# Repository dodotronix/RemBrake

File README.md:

# RemBrake - remote brake system for handbikes 

## Introduction
- TODO explain what the RemBrake, why we decided to create this project

### Assembling RemBrake
- TODO explain how to use the kicad data (use html ibom in web browser)
- TODO how to solder the modules on the RemBrake PCB
- TODO how to connect the wires

## Notes
* Pay attention that all the connectors are well soldered to the board.

### Prepare the module 
1) load the circuitpython to the QT Py RP2040
2) press and hold BOOT button and then press RST button
3) you should see now RPI partition mounted to your PC 
4) download CircuitPython bootloader (.uf2 file) from [circuitpython.org](https://circuitpython.org/board/adafruit_qtpy_rp2040/) 
5) drag and drop the file onto the partition
6) it takes few moments and you should see your partition name turn to CIRCUITPYTHON

### Upload RemBrake files + necessary modules
1) go to the folder fw folder
2) run $ make prepare
3) move the folder target to your CIRCPITPYTHON partition

## Features
- TODO how the PCB behaves (charging, running, error)
- TODO what the different colors mean

## About the system
### System's Block Diagram (BD) 
### System's Finite State Machine (FSM)

## Possible further development
- Bidirectional remote contoller that the assistant can see the battery status
- Accelerometer feedback, to adjust braking power according to the situation
- Using hydraulic piston actuator to move with the brake directly, which could shrink significantly the size of the package
- designing custom usb-c charger to avoid the hustle with unprecise power management of the chinese module

## Development

# ISSUES 
## Hardware
* When the brake power is cut, the display turns off but the shift register
inside stays powered enough to retain its latched state; as a result, when the
LED bar is powered again it lights from the old data and continues glowing for
up to 8s.
* The transition from charging to running is too slow, so reverse current is
feeding the base of the state-switching transistor and back-driving it;
swapping in a Schottky diode (or regular diode) with a higher forward drop
would block that reverse current and fix the issue.

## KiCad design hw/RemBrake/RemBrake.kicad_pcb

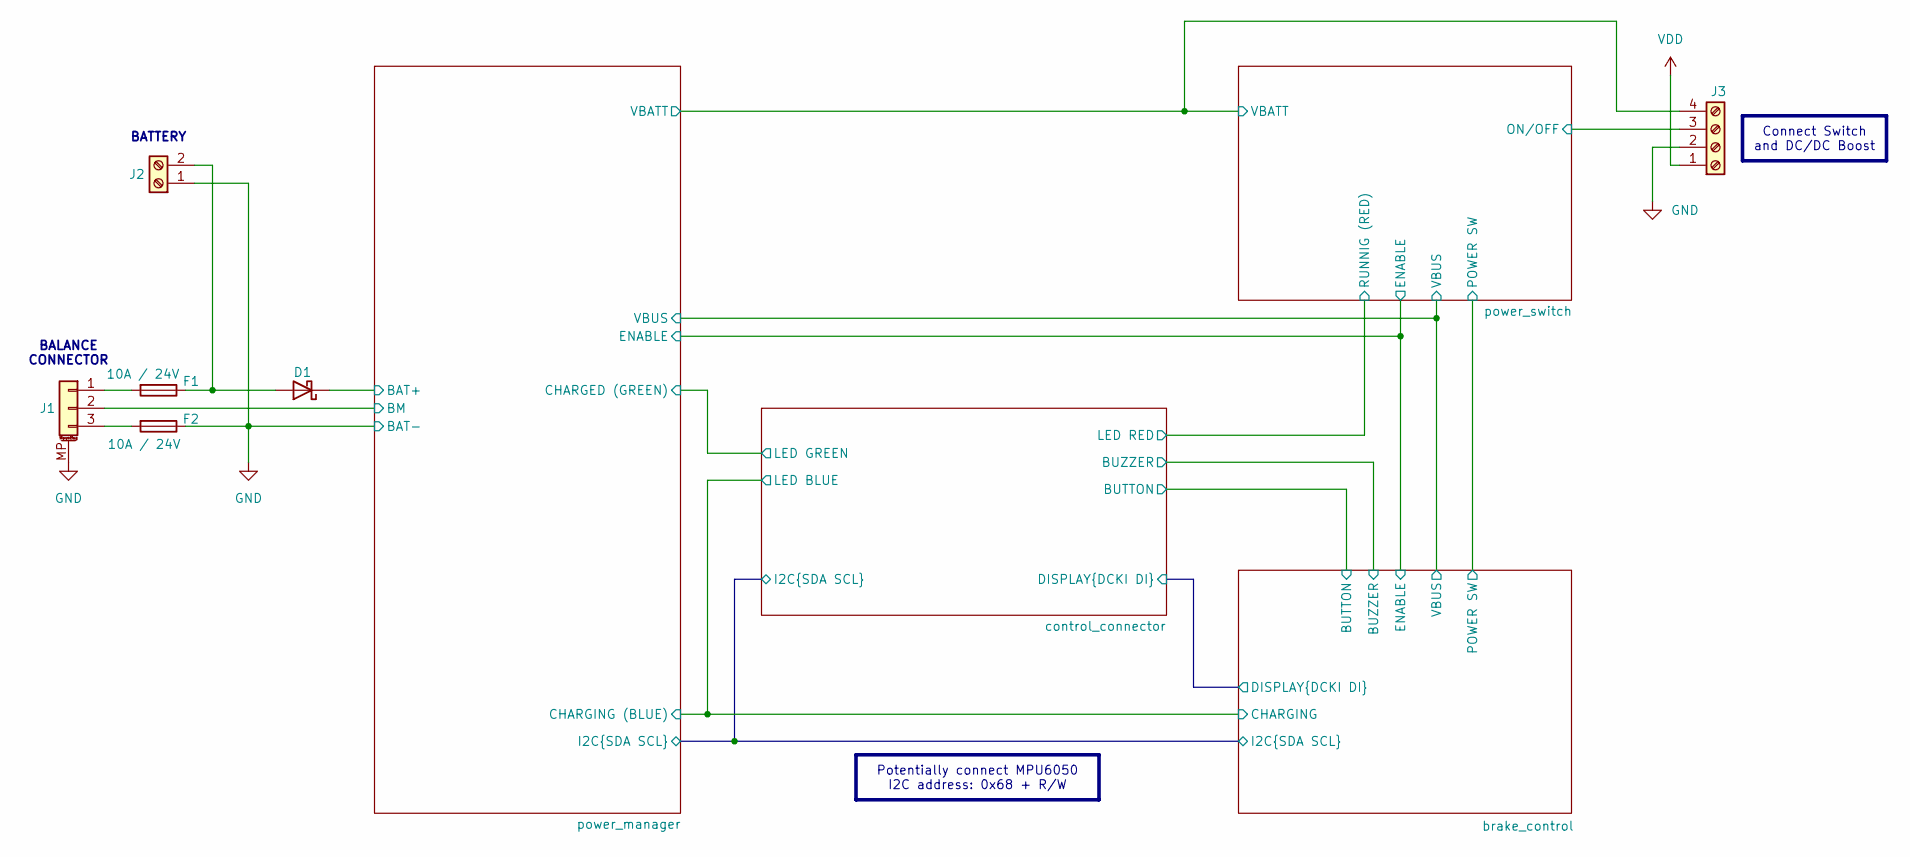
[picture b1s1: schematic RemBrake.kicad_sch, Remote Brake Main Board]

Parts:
D1: MBR0520; D_SMA
F1, F2: 10A / 24V; Fuse_1206_3216Metric_Pad1.42x1.75mm_HandSolder
J1: Conn_01x03_MountingPin; JST_XH_S3B-XH-SM4-TB_1x03-1MP_P2.50mm_Horizontal
J2: Screw_Terminal_01x02; TerminalBlock_Phoenix_MKDS-1,5-2_1x02_P5.00mm_Horizontal
J3: Screw_Terminal_01x04; TerminalBlock_Phoenix_MPT-0,5-4-2.54_1x04_P2.54mm_Horizontal

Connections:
/power_manager/BAT+: D1.1 (K); also elsewhere on the board
/power_manager/BM: J1.2; also elsewhere on the board
/power_manager/VBATT: J3.4; also elsewhere on the board
/power_switch/ON/OFF: J3.3; also elsewhere on the board
GND: F2.1, J1.MP (MountPin), J2.1, J3.2; also elsewhere on the board
unnamed: D1.2 (A), F1.1, J2.2
unnamed: F1.2, J1.1
unnamed: F2.2, J1.3
VDD: J3.1; also elsewhere on the board

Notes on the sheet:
BATTERY
BALANCE CONNECTOR
Potentially connect MPU6050 I2C address: 0x68 + R/W
Connect Switch and DC/DC Boost

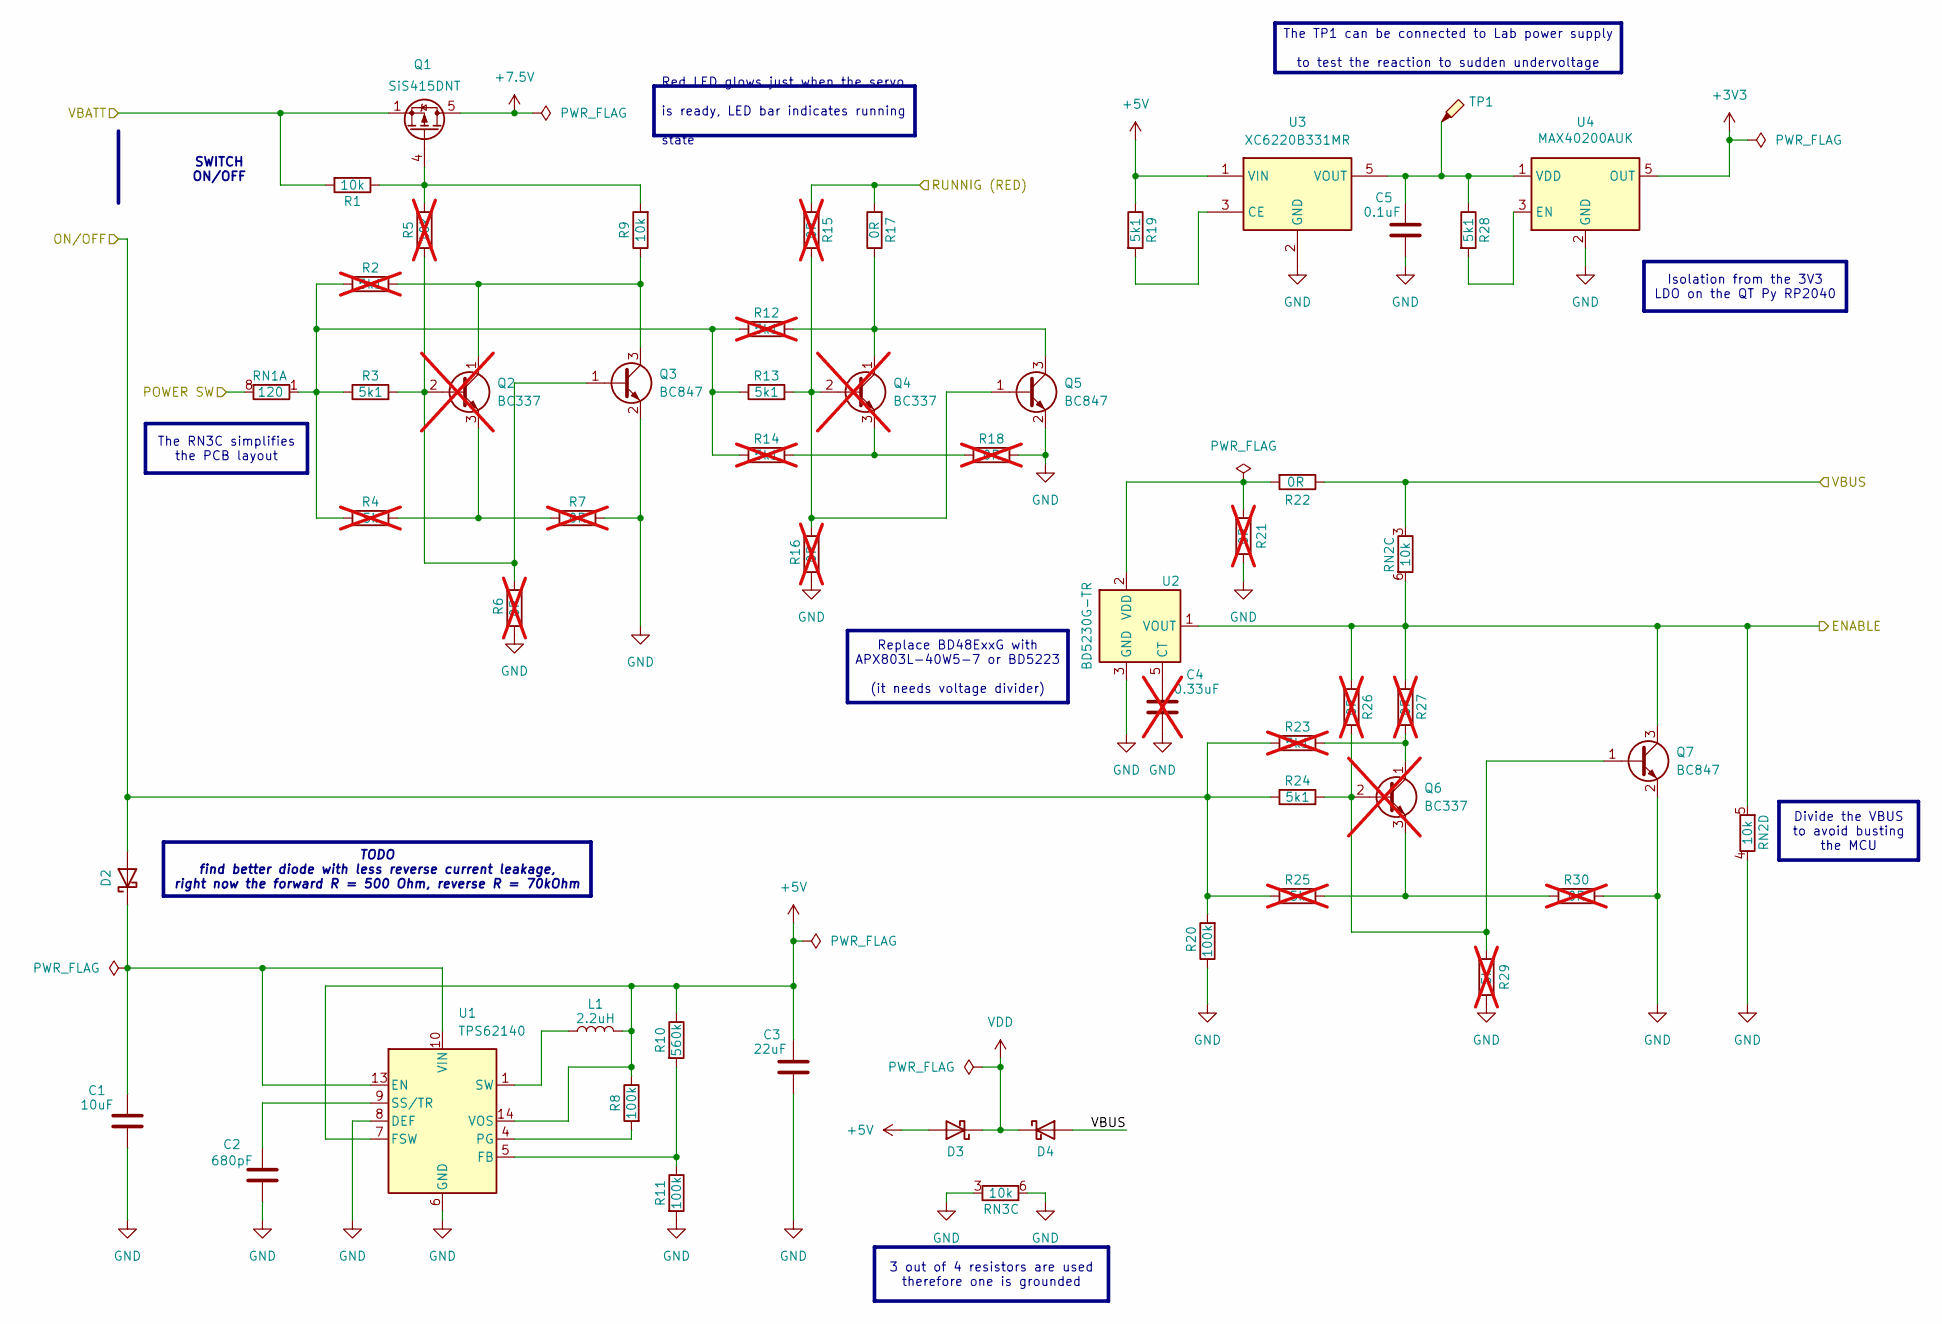
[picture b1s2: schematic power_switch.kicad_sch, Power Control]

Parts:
C1: 10uF; C_0805_2012Metric_Pad1.18x1.45mm_HandSolder
C2: 680pF; C_0805_2012Metric_Pad1.18x1.45mm_HandSolder
C3: 22uF; C_0805_2012Metric_Pad1.18x1.45mm_HandSolder
C4: 0.33uF; C_0805_2012Metric_Pad1.18x1.45mm_HandSolder; not fitted
C5: 0.1uF; C_0805_2012Metric_Pad1.18x1.45mm_HandSolder
D2: MBR0520; D_SMA
D3, D4: MBR0520; D_SOD-123
L1: 2.2uH; L_1008_2520Metric_Pad1.43x2.20mm_HandSolder
Q1: SiS415DNT; Vishay_PowerPAK_1212-8_Single
Q2, Q4, Q6: BC337; TO-92_Inline; not fitted
Q3, Q5, Q7: BC847; SOT-23
R1, R9: 10k; R_0805_2012Metric_Pad1.20x1.40mm_HandSolder
R2, R12, R14, R23: 5k1; R_0805_2012Metric_Pad1.20x1.40mm_HandSolder; not fitted
R3, R13, R19, R24, R28: 5k1; R_0805_2012Metric_Pad1.20x1.40mm_HandSolder
R4, R25, R29: 5k; R_0805_2012Metric_Pad1.20x1.40mm_HandSolder; not fitted
R5: 10k; R_0805_2012Metric_Pad1.20x1.40mm_HandSolder; not fitted
R6, R7, R15, R16, R18, R21, R26, R27, R30: 0R; R_0805_2012Metric_Pad1.20x1.40mm_HandSolder; not fitted
R8, R11, R20: 100k; R_0805_2012Metric_Pad1.20x1.40mm_HandSolder
R10: 560k; R_0805_2012Metric_Pad1.20x1.40mm_HandSolder
R17, R22: 0R; R_0805_2012Metric_Pad1.20x1.40mm_HandSolder
RN1: 120; R_Array_Concave_4x0603
RN2, RN3: 10k; R_Array_Convex_4x0603
TP1: TestPoint_Probe; TestPoint_Pad_1.5x1.5mm
U1: TPS62140; VQFN-16-1EP_3x3mm_P0.5mm_EP1.68x1.68mm_ThermalVias
U2: BD5230G-TR; SOT-23-5
U3: XC6220B331MR; SOT-23-5
U4: MAX40200AUK; SOT-23-5

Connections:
+3V3: U4.5 (OUT); also elsewhere on the board
+5V: C3.1, D3.2 (A), L1.2, R8.1, R10.1, R19.1, U1.7 (FSW), U1.14 (VOS), U3.1 (VIN); also elsewhere on the board
+7.5V: Q1.5 (D); also elsewhere on the board
/brake_control/ENABLE: Q7.3 (C), R26.2, R27.2, RN2.5 (R4.2), RN2.6 (R3.2), U2.1 (VOUT); also elsewhere on the board
/brake_control/POWER SW: RN1.8 (R1.2); also elsewhere on the board
/control_connector/LED RED: R15.2, R17.2; also elsewhere on the board
/power_manager/VBATT: Q1.1 (S), Q1.2 (S), Q1.3 (S), R1.2; also elsewhere on the board
/power_switch/ON/OFF: D2.2 (A), R20.2, R23.1, R24.1, R25.1; also elsewhere on the board
/power_switch/VBUS: D4.2 (A), R22.1, RN2.3 (R3.1); also elsewhere on the board
GND: C1.2, C2.2, C3.2, C4.2, C5.2, Q3.2 (E), Q5.2 (E), Q7.2 (E), R6.1, R7.1, R11.2, R16.1, R18.1, R20.1, R21.2, R29.1, R30.1, RN2.4 (R4.1), RN3.3 (R3.1), RN3.6 (R3.2), U1.6 (GND), U1.8 (DEF), U1.15 (GND), U1.16 (GND), U1.17 (GND), U2.3 (GND), U3.2 (GND), U4.2 (GND); also elsewhere on the board
unnamed: C1.1, D2.1 (K), U1.10 (VIN), U1.11 (VIN), U1.12 (VIN), U1.13 (EN)
unnamed: L1.1, U1.1 (SW), U1.2 (SW), U1.3 (SW)
unnamed: Q1.4 (G), R1.1, R5.2, R9.2
unnamed: Q2.2 (B), Q3.1 (B), R3.2, R5.1, R6.2
unnamed: Q2.1 (C), Q3.3 (C), R2.2, R9.1
unnamed: Q2.3 (E), R4.2, R7.2
unnamed: Q4.2 (B), Q5.1 (B), R13.2, R15.1, R16.2
unnamed: Q4.1 (C), Q5.3 (C), R12.2, R17.1
unnamed: Q4.3 (E), R14.2, R18.2
unnamed: Q6.2 (B), Q7.1 (B), R24.2, R26.1, R29.2
unnamed: Q6.1 (C), R23.2, R27.1
unnamed: Q6.3 (E), R25.2, R30.2
unnamed: R2.1, R3.1, R4.1, R12.1, R13.1, R14.1, RN1.1 (R1.1)
unnamed: R10.2, R11.1, U1.5 (FB)
unnamed: R8.2, U1.4 (PG)
unnamed: C2.1, U1.9 (SS/TR)
unnamed: C4.1, U2.5 (CT)
unnamed: R21.1, R22.2, U2.2 (VDD)
unnamed: R19.2, U3.3 (CE)
unnamed: C5.1, R28.1, TP1.1, U3.5 (VOUT), U4.1 (VDD)
unnamed: R28.2, U4.3 (EN)
VDD: D3.1 (K), D4.1 (K); also elsewhere on the board

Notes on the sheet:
SWITCH ON/OFF
Divide the VBUS to avoid busting the MCU
Red LED glows just when the servo is ready, LED bar indicates running state
Replace BD48ExxG with APX803L-40W5-7 or BD5223 (it needs voltage divider)
TODO find better diode with less reverse current leakage, right now the forward R = 500 Ohm, reverse R = 70kOhm
Isolation from the 3V3 LDO on the QT Py RP2040
The TP1 can be connected to Lab power supply to test the reaction to sudden undervoltage
The RN3C simplifies the PCB layout
3 out of 4 resistors are used therefore one is grounded

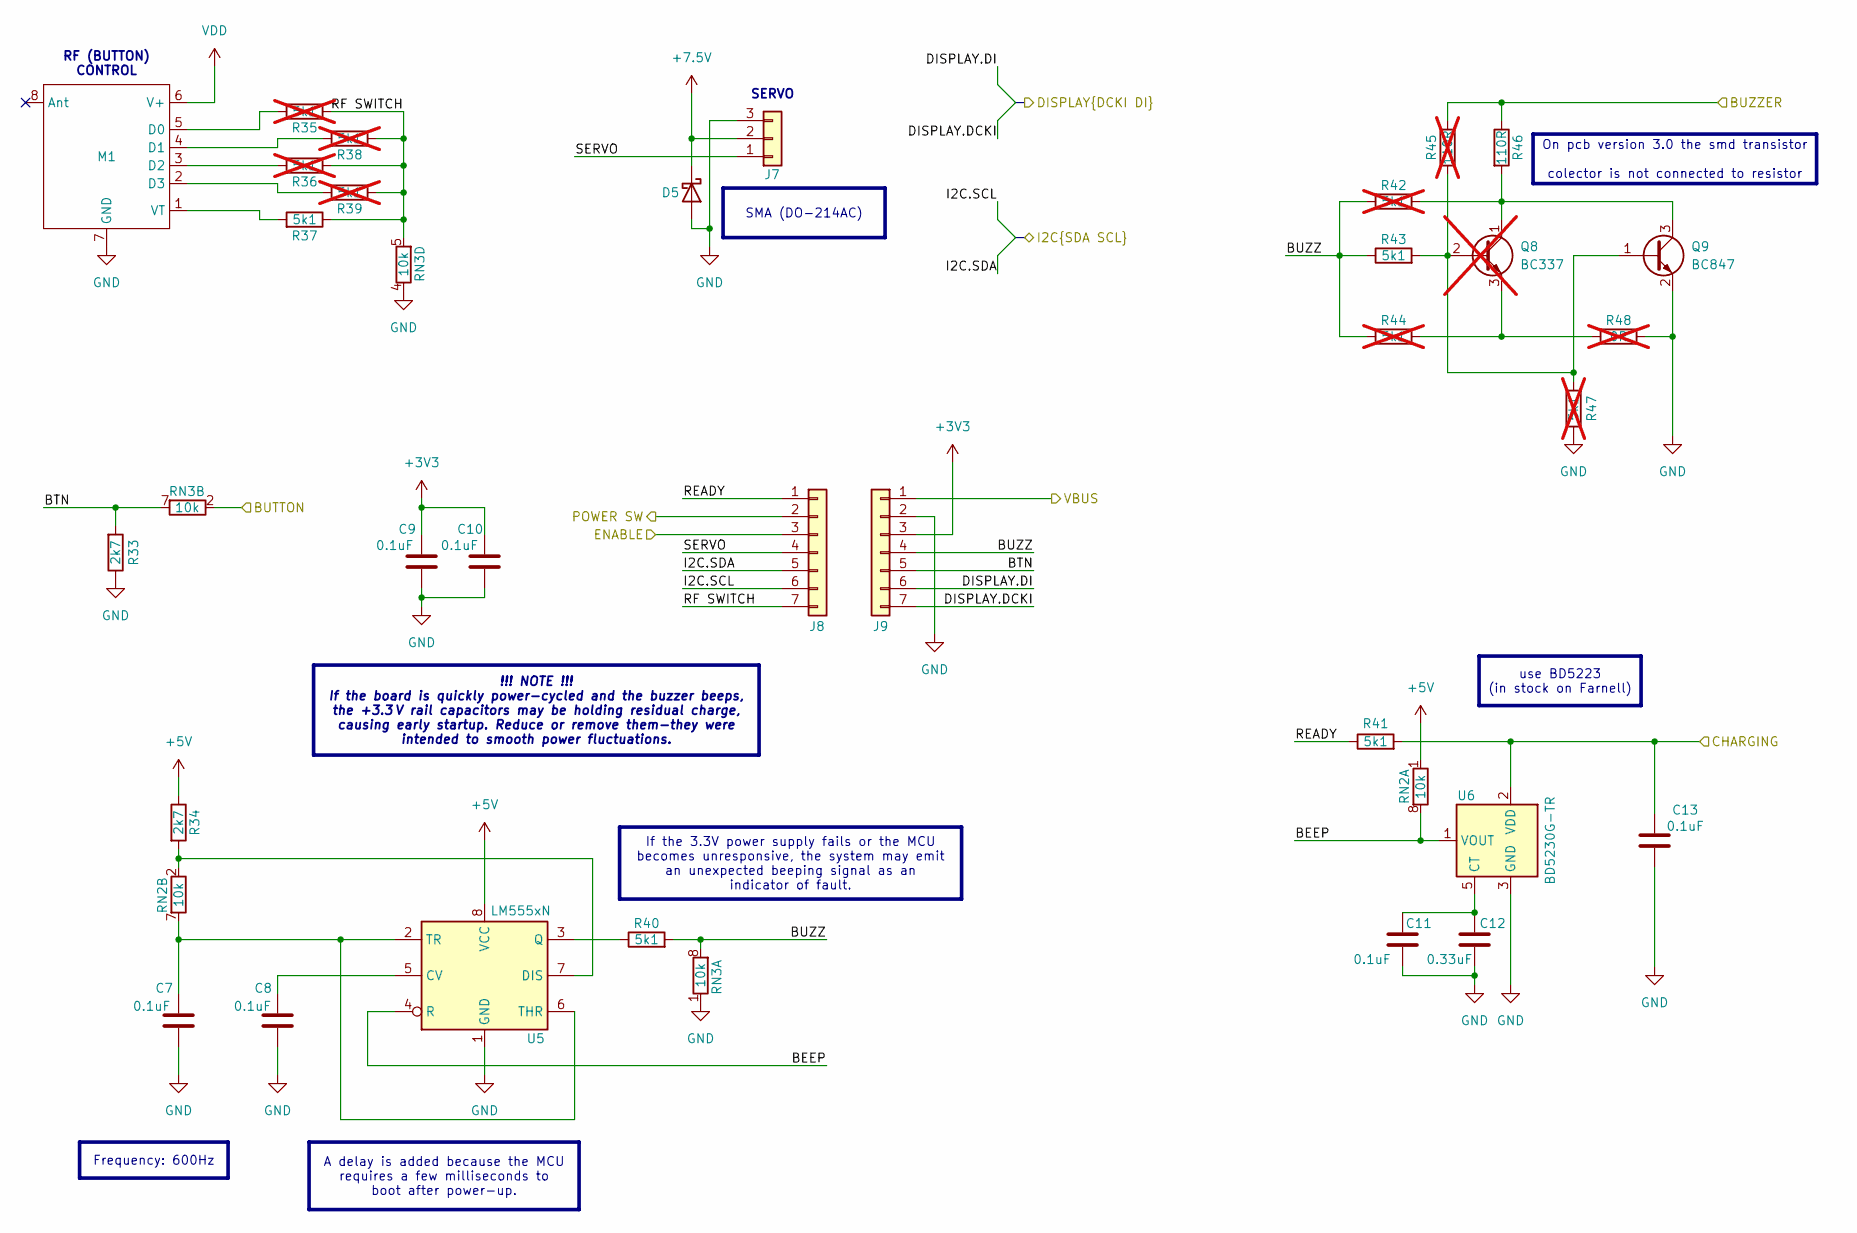
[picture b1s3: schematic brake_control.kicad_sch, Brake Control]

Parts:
C7, C8, C9, C10, C11, C13: 0.1uF; C_0805_2012Metric_Pad1.18x1.45mm_HandSolder
C12: 0.33uF; C_0805_2012Metric_Pad1.18x1.45mm_HandSolder
D5: SS1200; D_SMA
J7: Conn_01x03; PinHeader_1x03_P2.54mm_Vertical_SMD_Pin1Left
J8, J9: Conn_01x07; PinSocket_1x07_P2.54mm_Vertical_SMD_Pin1Left
M1: RF_controller
Q8: BC337; TO-92_Inline; not fitted
Q9: BC847; SOT-23
R33, R34: 2k7; R_0805_2012Metric_Pad1.20x1.40mm_HandSolder
R35, R36, R38, R39, R42, R44, R47: 5k1; R_0805_2012Metric_Pad1.20x1.40mm_HandSolder; not fitted
R37, R40, R41, R43: 5k1; R_0805_2012Metric_Pad1.20x1.40mm_HandSolder
R45: 110R; R_0805_2012Metric_Pad1.20x1.40mm_HandSolder; not fitted
R46: 110R; R_0805_2012Metric_Pad1.20x1.40mm_HandSolder
R48: 0R; R_0805_2012Metric_Pad1.20x1.40mm_HandSolder; not fitted
RN2, RN3: 10k; R_Array_Convex_4x0603
U5: LM555xN; DIP-8_W7.62mm
U6: BD5230G-TR; SOT-23-5

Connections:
+3V3: C9.1, C10.1, J9.3; also elsewhere on the board
+5V: R34.1, RN2.1 (R1.1), U5.8 (VCC); also elsewhere on the board
+7.5V: D5.1 (K), J7.2; also elsewhere on the board
/brake_control/BEEP: RN2.8 (R1.2), U5.4 (R), U6.1 (VOUT)
/brake_control/BTN: J9.5, R33.2, RN3.7 (R2.2)
/brake_control/BUZZ: J9.4, R40.2, R42.2, R43.1, R44.1, RN3.8 (R1.2)
/brake_control/CHARGING: C13.1, R41.2, U6.2 (VDD); also elsewhere on the board
/brake_control/DISPLAY.DCKI: J9.7; also elsewhere on the board
/brake_control/DISPLAY.DI: J9.6; also elsewhere on the board
/brake_control/ENABLE: J8.3; also elsewhere on the board
/brake_control/I2C.SCL: J8.6; also elsewhere on the board
/brake_control/I2C.SDA: J8.5; also elsewhere on the board
/brake_control/POWER SW: J8.2; also elsewhere on the board
/brake_control/READY: J8.1, R41.1
/brake_control/RF SWITCH: J8.7, R35.1, R36.1, R37.1, R38.1, R39.1, RN3.5 (R4.2)
/brake_control/SERVO: J7.1, J8.4
/control_connector/BUTTON: RN3.2 (R2.1); also elsewhere on the board
/control_connector/BUZZER: R45.1, R46.1; also elsewhere on the board
/power_switch/VBUS: J9.1; also elsewhere on the board
GND: C7.2, C8.2, C9.2, C10.2, C11.2, C12.2, C13.2, D5.2 (A), J7.3, J9.2, M1.7 (GND), Q9.2 (E), R33.1, R47.1, R48.1, RN3.1 (R1.1), RN3.4 (R4.1), U5.1 (GND), U6.3 (GND); also elsewhere on the board
unnamed: M1.5 (D0), R35.2
unnamed: M1.4 (D1), R38.2
unnamed: M1.3 (D2), R36.2
unnamed: M1.2 (D3), R39.2
unnamed: M1.1 (VT), R37.2
unnamed: Q8.2 (B), Q9.1 (B), R43.2, R45.2, R47.2
unnamed: Q8.1 (C), Q9.3 (C), R42.1, R46.2
unnamed: Q8.3 (E), R44.2, R48.2
unnamed: R34.2, RN2.2 (R2.1), U5.7 (DIS)
unnamed: C7.1, RN2.7 (R2.2), U5.2 (TR), U5.6 (THR)
unnamed: C8.1, U5.5 (CV)
unnamed: R40.1, U5.3 (Q)
unnamed: C11.1, C12.1, U6.5 (CT)
VDD: M1.6 (V+); also elsewhere on the board

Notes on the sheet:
SERVO
RF (BUTTON) CONTROL
SMA (DO-214AC)
!!! NOTE !!! If the board is quickly power-cycled and the buzzer beeps, the +3.3 V rail capacitors may be holding residual charge, causing early startup. Reduce or remove them-they were intended to smooth power fluctuations.
A delay is added because the MCU requires a few milliseconds to boot after power-up.
use BD5223 (in stock on Farnell)
Frequency: 600Hz
On pcb version 3.0 the smd transistor colector is not connected to resistor
If the 3.3V power supply fails or the MCU becomes unresponsive, the system may emit an unexpected beeping signal as an indicator of fault.

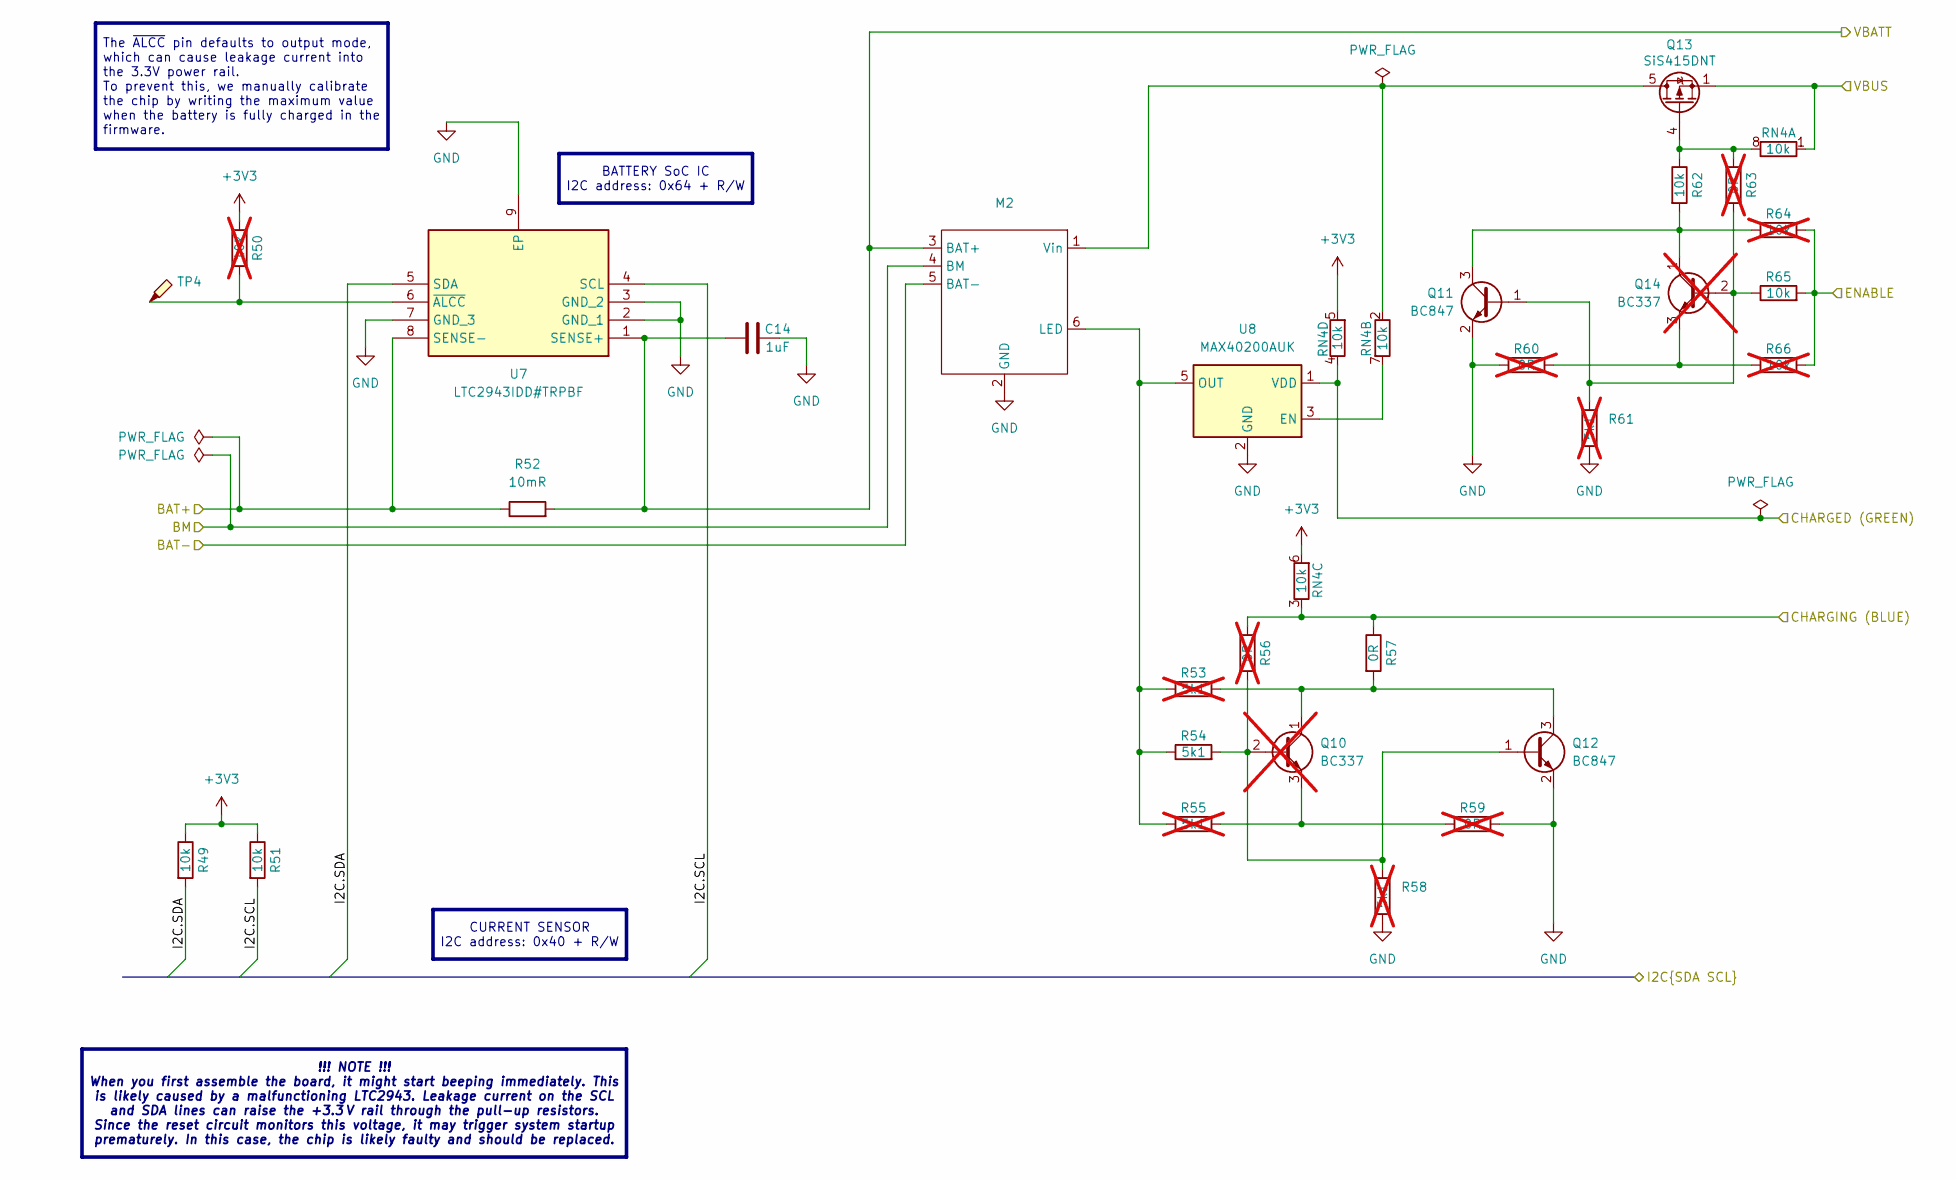
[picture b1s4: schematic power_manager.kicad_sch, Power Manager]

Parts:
C14: 1uF; C_0805_2012Metric_Pad1.18x1.45mm_HandSolder
M2: USBC_charger
Q10, Q14: BC337; TO-92_Inline; not fitted
Q11, Q12: BC847; SOT-23
Q13: SiS415DNT; Vishay_PowerPAK_1212-8_Single
R49, R51, R62, R65: 10k; R_0805_2012Metric_Pad1.20x1.40mm_HandSolder
R50, R64, R66: 10k; R_0805_2012Metric_Pad1.20x1.40mm_HandSolder; not fitted
R52: 10mR; R_2512_6332Metric_Pad1.40x3.35mm_HandSolder
R53, R55, R58, R61: 5k1; R_0805_2012Metric_Pad1.20x1.40mm_HandSolder; not fitted
R54: 5k1; R_0805_2012Metric_Pad1.20x1.40mm_HandSolder
R56, R59, R60, R63: 0R; R_0805_2012Metric_Pad1.20x1.40mm_HandSolder; not fitted
R57: 0R; R_0805_2012Metric_Pad1.20x1.40mm_HandSolder
RN4: 10k; R_Array_Convex_4x0603
TP4: TestPoint_Probe; TestPoint_Pad_1.5x1.5mm
U7: LTC2943IDD#TRPBF; DFN-8-1EP_3x3mm_P0.5mm_EP1.66x2.38mm; Mouser Part Number 584-LTC2943IDD#TRPBF
U8: MAX40200AUK; SOT-23-5

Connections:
+3V3: R49.1, R50.1, R51.1, RN4.5 (R4.2), RN4.6 (R3.2); also elsewhere on the board
/brake_control/CHARGING: R56.1, R57.1, RN4.3 (R3.1); also elsewhere on the board
/brake_control/ENABLE: R64.2, R65.2, R66.2; also elsewhere on the board
/brake_control/I2C.SCL: R51.2, U7.4 (SCL); also elsewhere on the board
/brake_control/I2C.SDA: R49.2, U7.5 (SDA); also elsewhere on the board
/control_connector/LED GREEN: RN4.4 (R4.1), U8.1 (VDD); also elsewhere on the board
/power_manager/BAT+: R52.1, U7.8 (SENSE-); also elsewhere on the board
/power_manager/BM: M2.4 (BM); also elsewhere on the board
/power_manager/VBATT: C14.2, M2.3 (BAT+), R52.2, U7.1 (SENSE+); also elsewhere on the board
/power_switch/VBUS: Q13.1 (S), Q13.2 (S), Q13.3 (S), RN4.1 (R1.1); also elsewhere on the board
GND: C14.1, M2.2 (GND), M2.5 (BAT-), Q11.2 (E), Q12.2 (E), R58.1, R59.1, R60.2, R61.1, U7.2 (GND_1), U7.3 (GND_2), U7.7 (GND_3), U7.9 (EP), U8.2 (GND); also elsewhere on the board
unnamed: M2.6 (LED), R53.1, R54.1, R55.1, U8.5 (OUT)
unnamed: M2.1 (Vin), Q13.5 (D), RN4.2 (R2.1)
unnamed: Q10.2 (B), Q12.1 (B), R54.2, R56.2, R58.2
unnamed: Q10.1 (C), Q12.3 (C), R53.2, R57.2
unnamed: Q10.3 (E), R55.2, R59.2
unnamed: Q11.1 (B), Q14.2 (B), R61.2, R63.2, R65.1
unnamed: Q11.3 (C), Q14.1 (C), R62.2, R64.1
unnamed: Q13.4 (G), R62.1, R63.1, RN4.8 (R1.2)
unnamed: Q14.3 (E), R60.1, R66.1
unnamed: RN4.7 (R2.2), U8.3 (EN)
unnamed: R50.2, TP4.1, U7.6 (~ALCC)

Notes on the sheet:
!!! NOTE !!! When you first assemble the board, it might start beeping immediately. This is likely caused by a malfunctioning LTC2943. Leakage current on the SCL and SDA lines can raise the +3.3 V rail through the pull-up resistors. Since the reset circuit monitors this voltage, it may trigger syst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
BATTERY SoC IC I2C address: 0x64 + R/W
The ~{ALCC} pin defaults to output mode, which can cause leakage current into the 3.3V power rail. To prevent this, we manually calibrate the chip by writing the maximum value when the battery is fully charged in the firmware.
CURRENT SENSOR I2C address: 0x40 + R/W

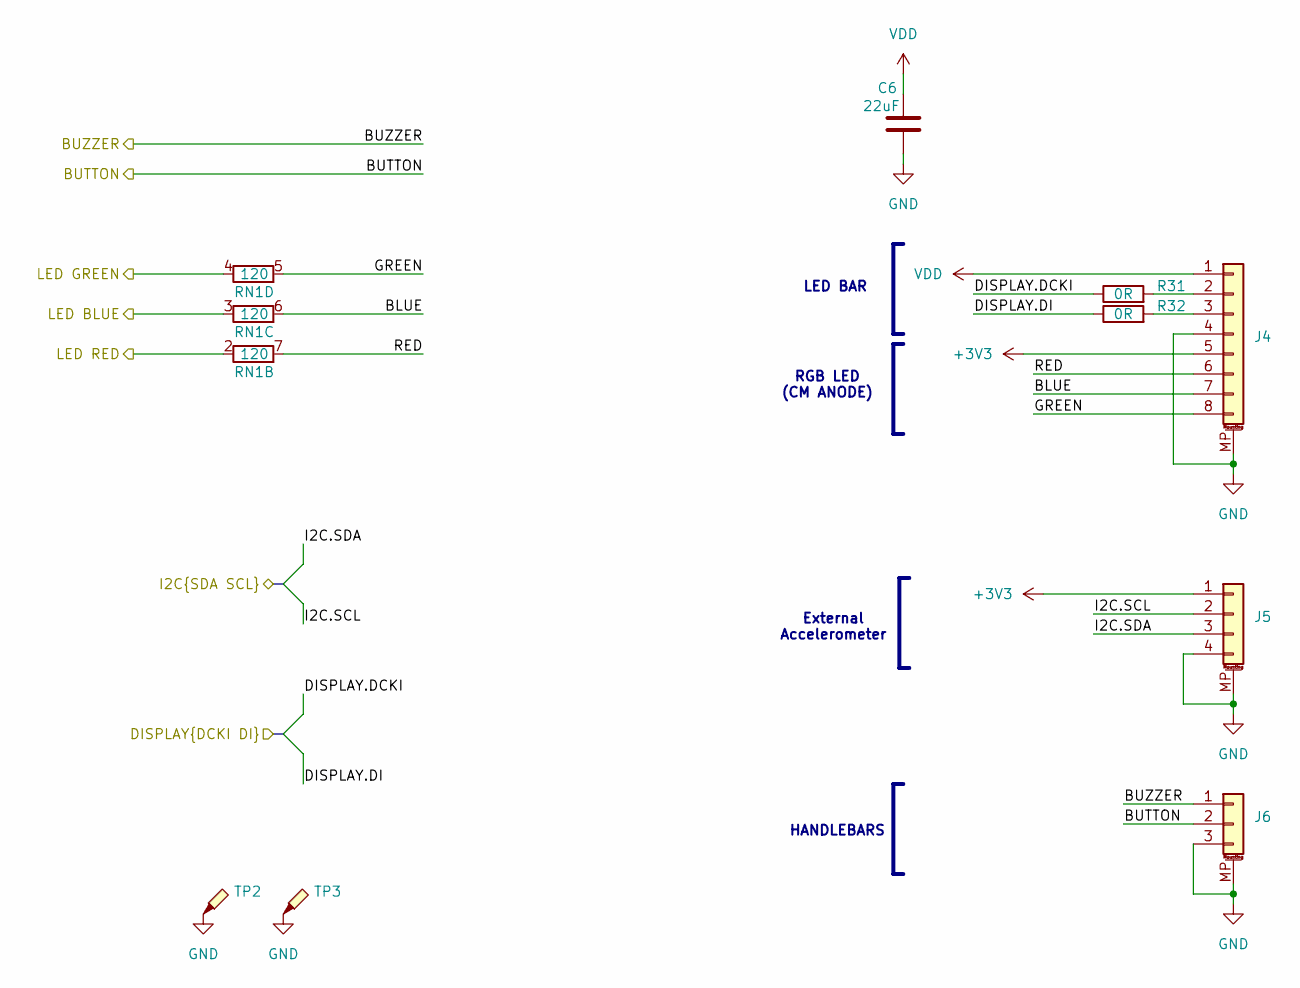
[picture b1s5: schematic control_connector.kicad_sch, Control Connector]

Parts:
C6: 22uF; C_0805_2012Metric_Pad1.18x1.45mm_HandSolder
J4: Conn_01x08_MountingPin; Molex_CLIK-Mate_502494-0870_1x08-1MP_P2.00mm_Horizontal
J5: Conn_01x04_MountingPin; Molex_CLIK-Mate_502494-0470_1x04-1MP_P2.00mm_Horizontal
J6: Conn_01x03_MountingPin; Molex_CLIK-Mate_502494-0370_1x03-1MP_P2.00mm_Horizontal
R31, R32: 0R; R_0805_2012Metric_Pad1.20x1.40mm_HandSolder
RN1: 120; R_Array_Concave_4x0603
TP2, TP3: TestPoint_Probe; TestPoint_Pad_1.5x1.5mm

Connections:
+3V3: J4.5, J5.1; also elsewhere on the board
/brake_control/CHARGING: RN1.3 (R3.1); also elsewhere on the board
/brake_control/DISPLAY.DCKI: R31.1; also elsewhere on the board
/brake_control/DISPLAY.DI: R32.1; also elsewhere on the board
/brake_control/I2C.SCL: J5.2; also elsewhere on the board
/brake_control/I2C.SDA: J5.3; also elsewhere on the board
/control_connector/BLUE: J4.7, RN1.6 (R3.2)
/control_connector/BUTTON: J6.2; also elsewhere on the board
/control_connector/BUZZER: J6.1; also elsewhere on the board
/control_connector/GREEN: J4.8, RN1.5 (R4.2)
/control_connector/LED GREEN: RN1.4 (R4.1); also elsewhere on the board
/control_connector/LED RED: RN1.2 (R2.1); also elsewhere on the board
/control_connector/RED: J4.6, RN1.7 (R2.2)
GND: C6.2, J4.4, J4.MP (MountPin), J5.4, J5.MP (MountPin), J6.3, J6.MP (MountPin), TP2.1, TP3.1; also elsewhere on the board
unnamed: J4.2, R31.2
unnamed: J4.3, R32.2
VDD: C6.1, J4.1; also elsewhere on the board

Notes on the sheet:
RGB LED (CM ANODE)
External Accelerometer
HANDLEBARS
LED BAR

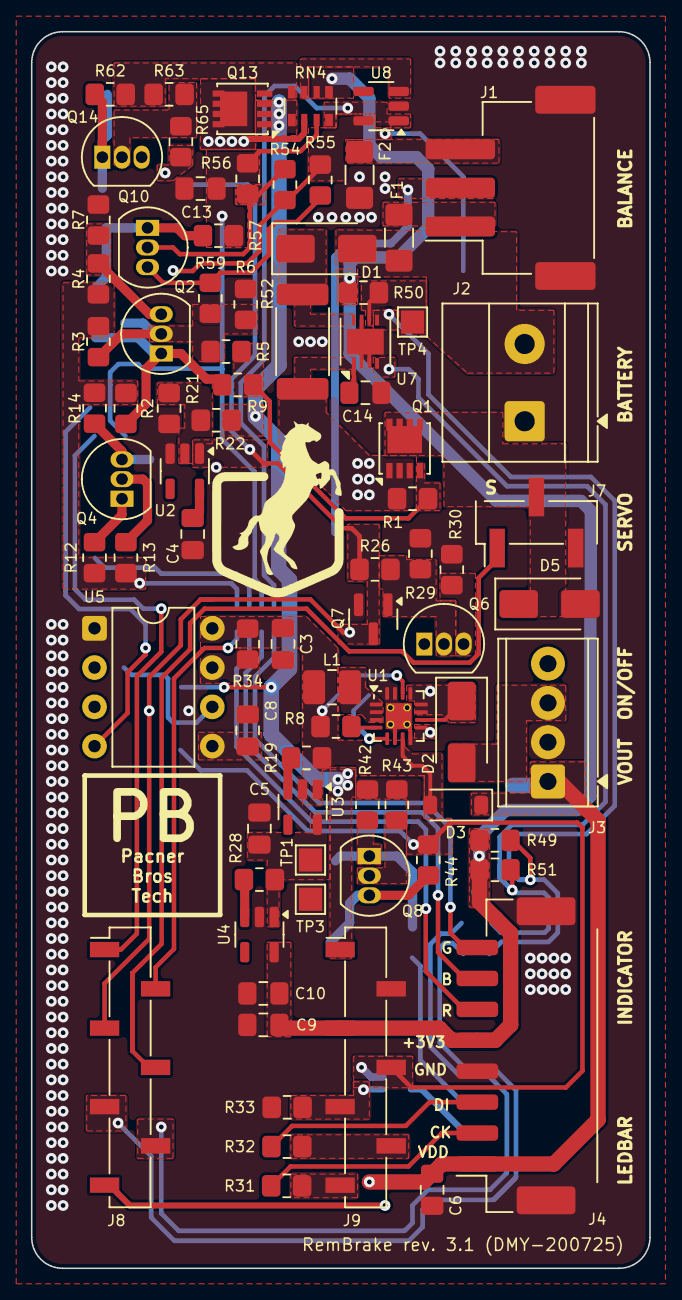
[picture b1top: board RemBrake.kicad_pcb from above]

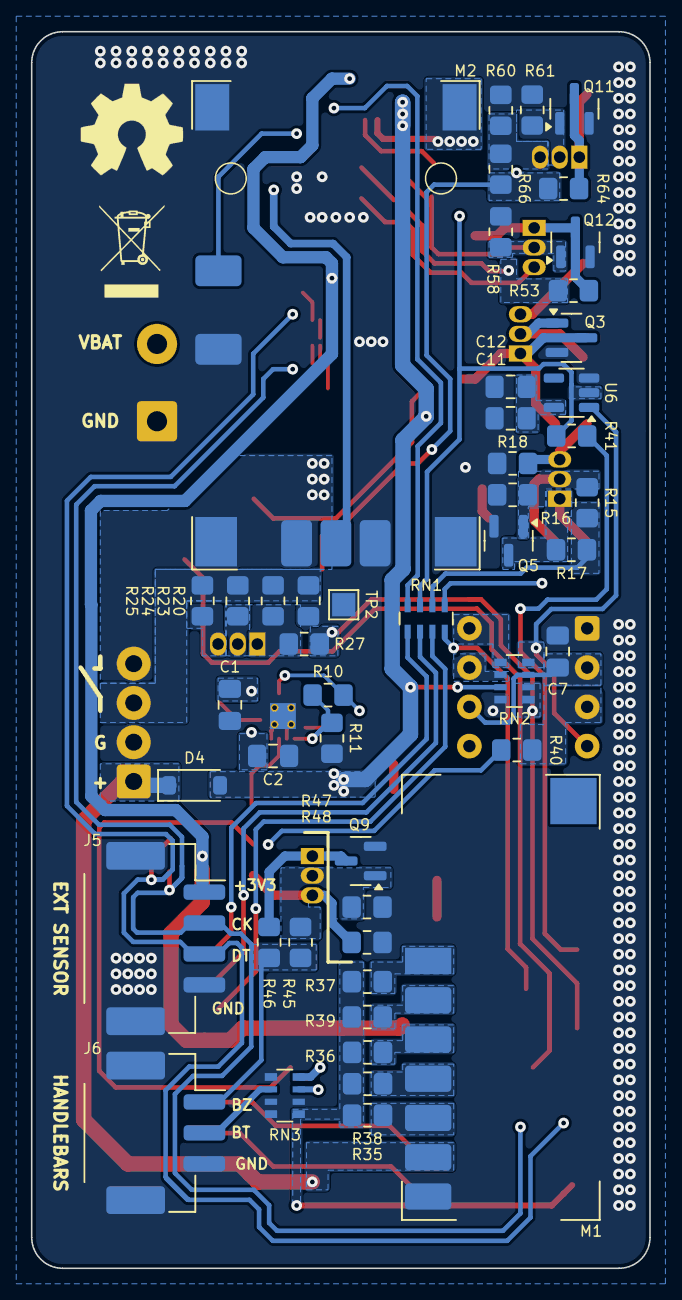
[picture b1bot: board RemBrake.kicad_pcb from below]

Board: 2 copper layers, 40.0 x 80.0 mm, 131 parts (50 on the bottom side), 80 nets.

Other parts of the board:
LOGO1: OSHW-Symbol_6.7x6mm_SilkScreen
LOGO2: WEEE-Logo_4.2x6mm_SilkScreen
